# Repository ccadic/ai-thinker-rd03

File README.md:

# ai-thinker-rd03
ai-thinker-rd03 kicad footprint - symbol and 3D files

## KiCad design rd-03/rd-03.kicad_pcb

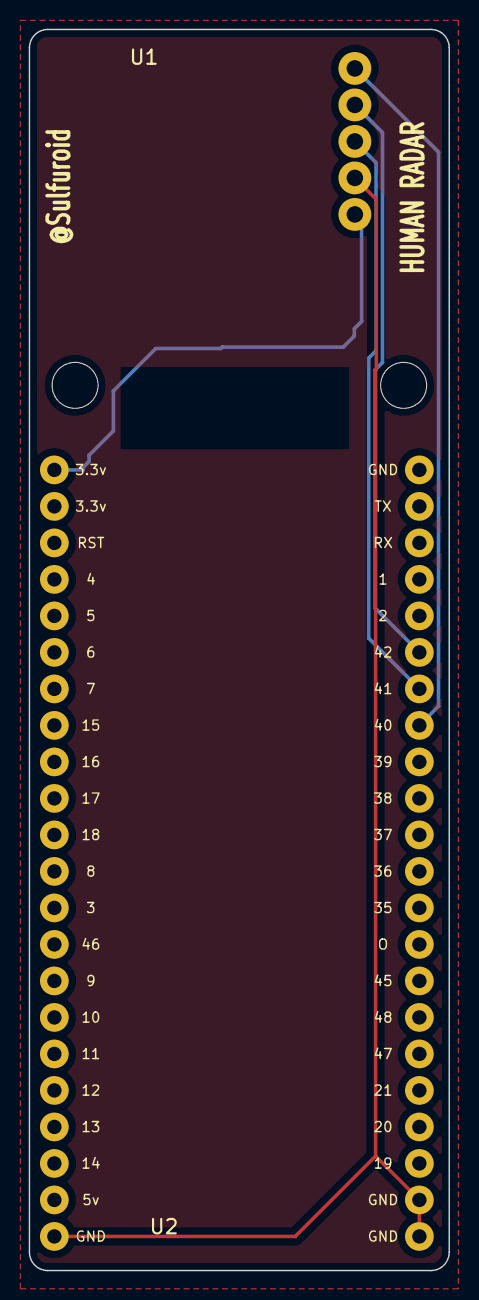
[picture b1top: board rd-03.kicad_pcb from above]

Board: 2 copper layers, 29.2 x 86.4 mm, 4 parts (0 on the bottom side), 5 nets.

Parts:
H1, H2: MountingHole; MountingHole_3.2mm_M3
U1: RD-03
U2: AI-S3

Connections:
+3.3V: U1.5 (3.3), U2.1 (3.3)
/GPIO41: U1.3 (OT1), U2.38 (41)
/GPIO42: U1.2 (RX), U2.39 (42)
/OT2: U1.1 (OT2), U2.37 (40)
GND: U1.4 (GND), U2.22 (GND), U2.23 (GND), U2.24 (GND)
